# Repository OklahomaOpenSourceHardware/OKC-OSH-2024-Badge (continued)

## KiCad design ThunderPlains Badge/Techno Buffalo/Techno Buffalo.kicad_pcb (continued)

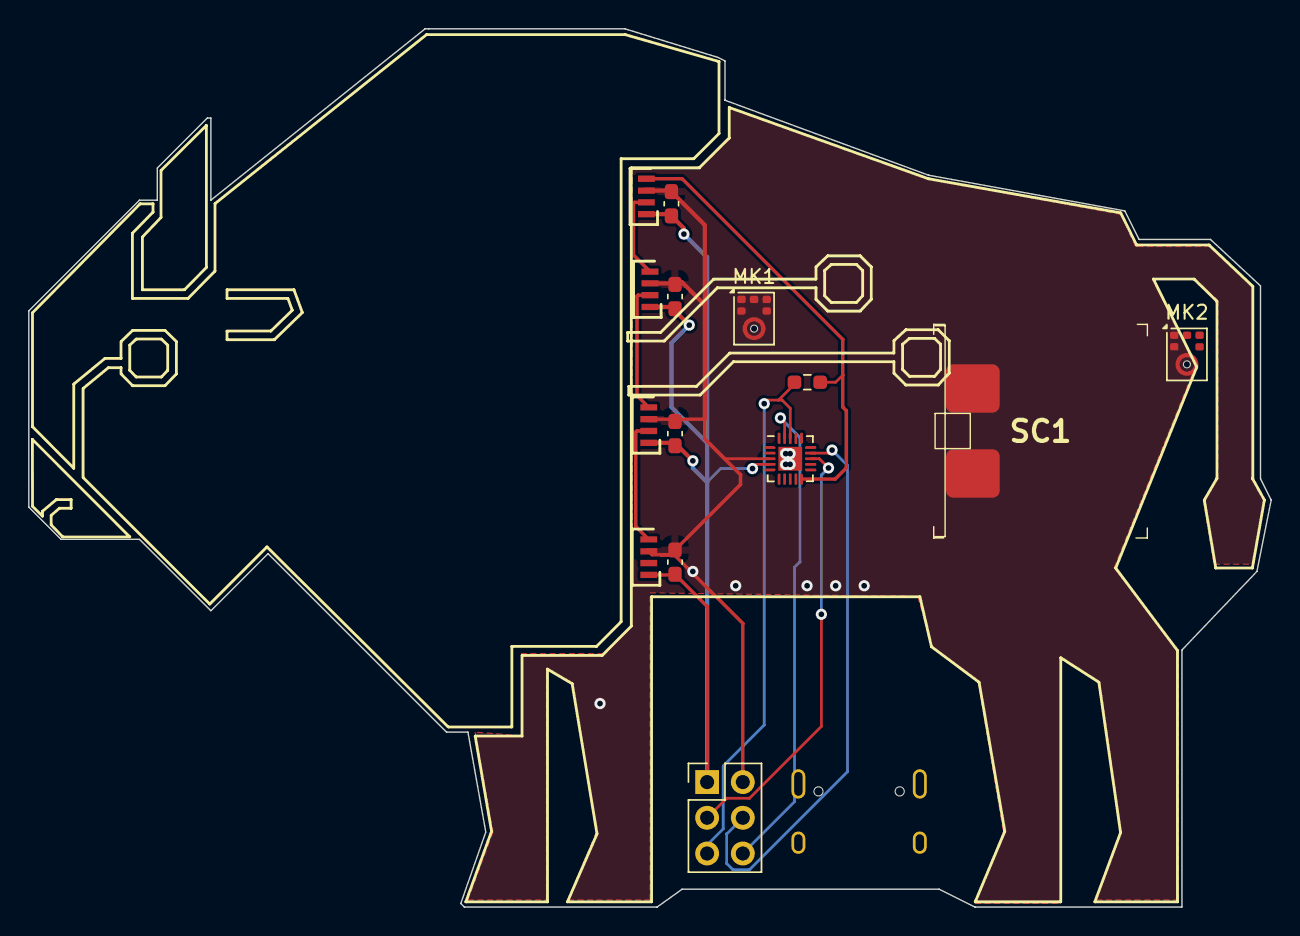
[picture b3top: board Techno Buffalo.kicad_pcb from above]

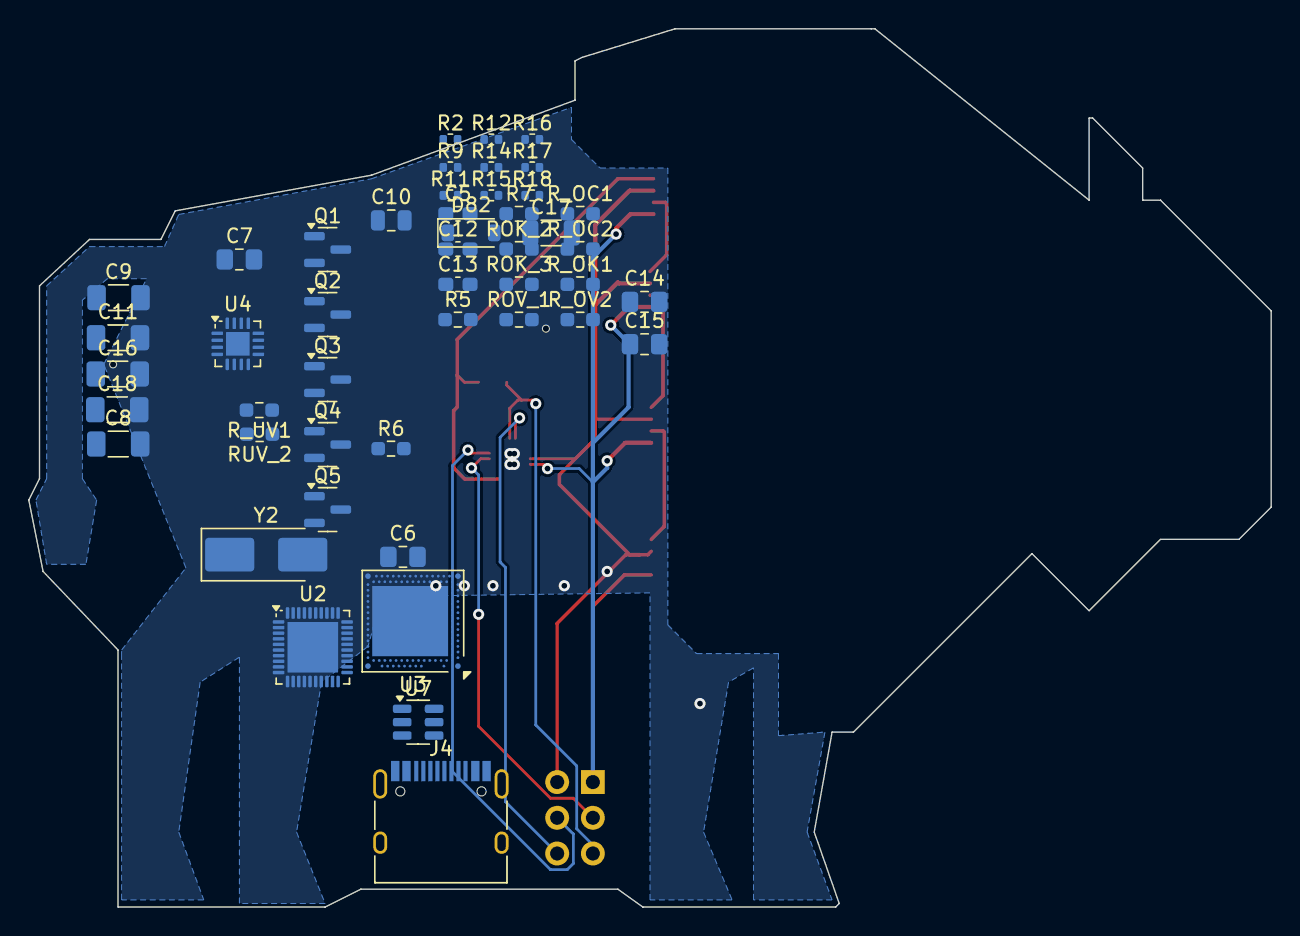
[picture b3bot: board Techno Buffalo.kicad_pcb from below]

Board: 2 copper layers, 88.4 x 62.5 mm, 61 parts (47 on the bottom side), 39 nets.

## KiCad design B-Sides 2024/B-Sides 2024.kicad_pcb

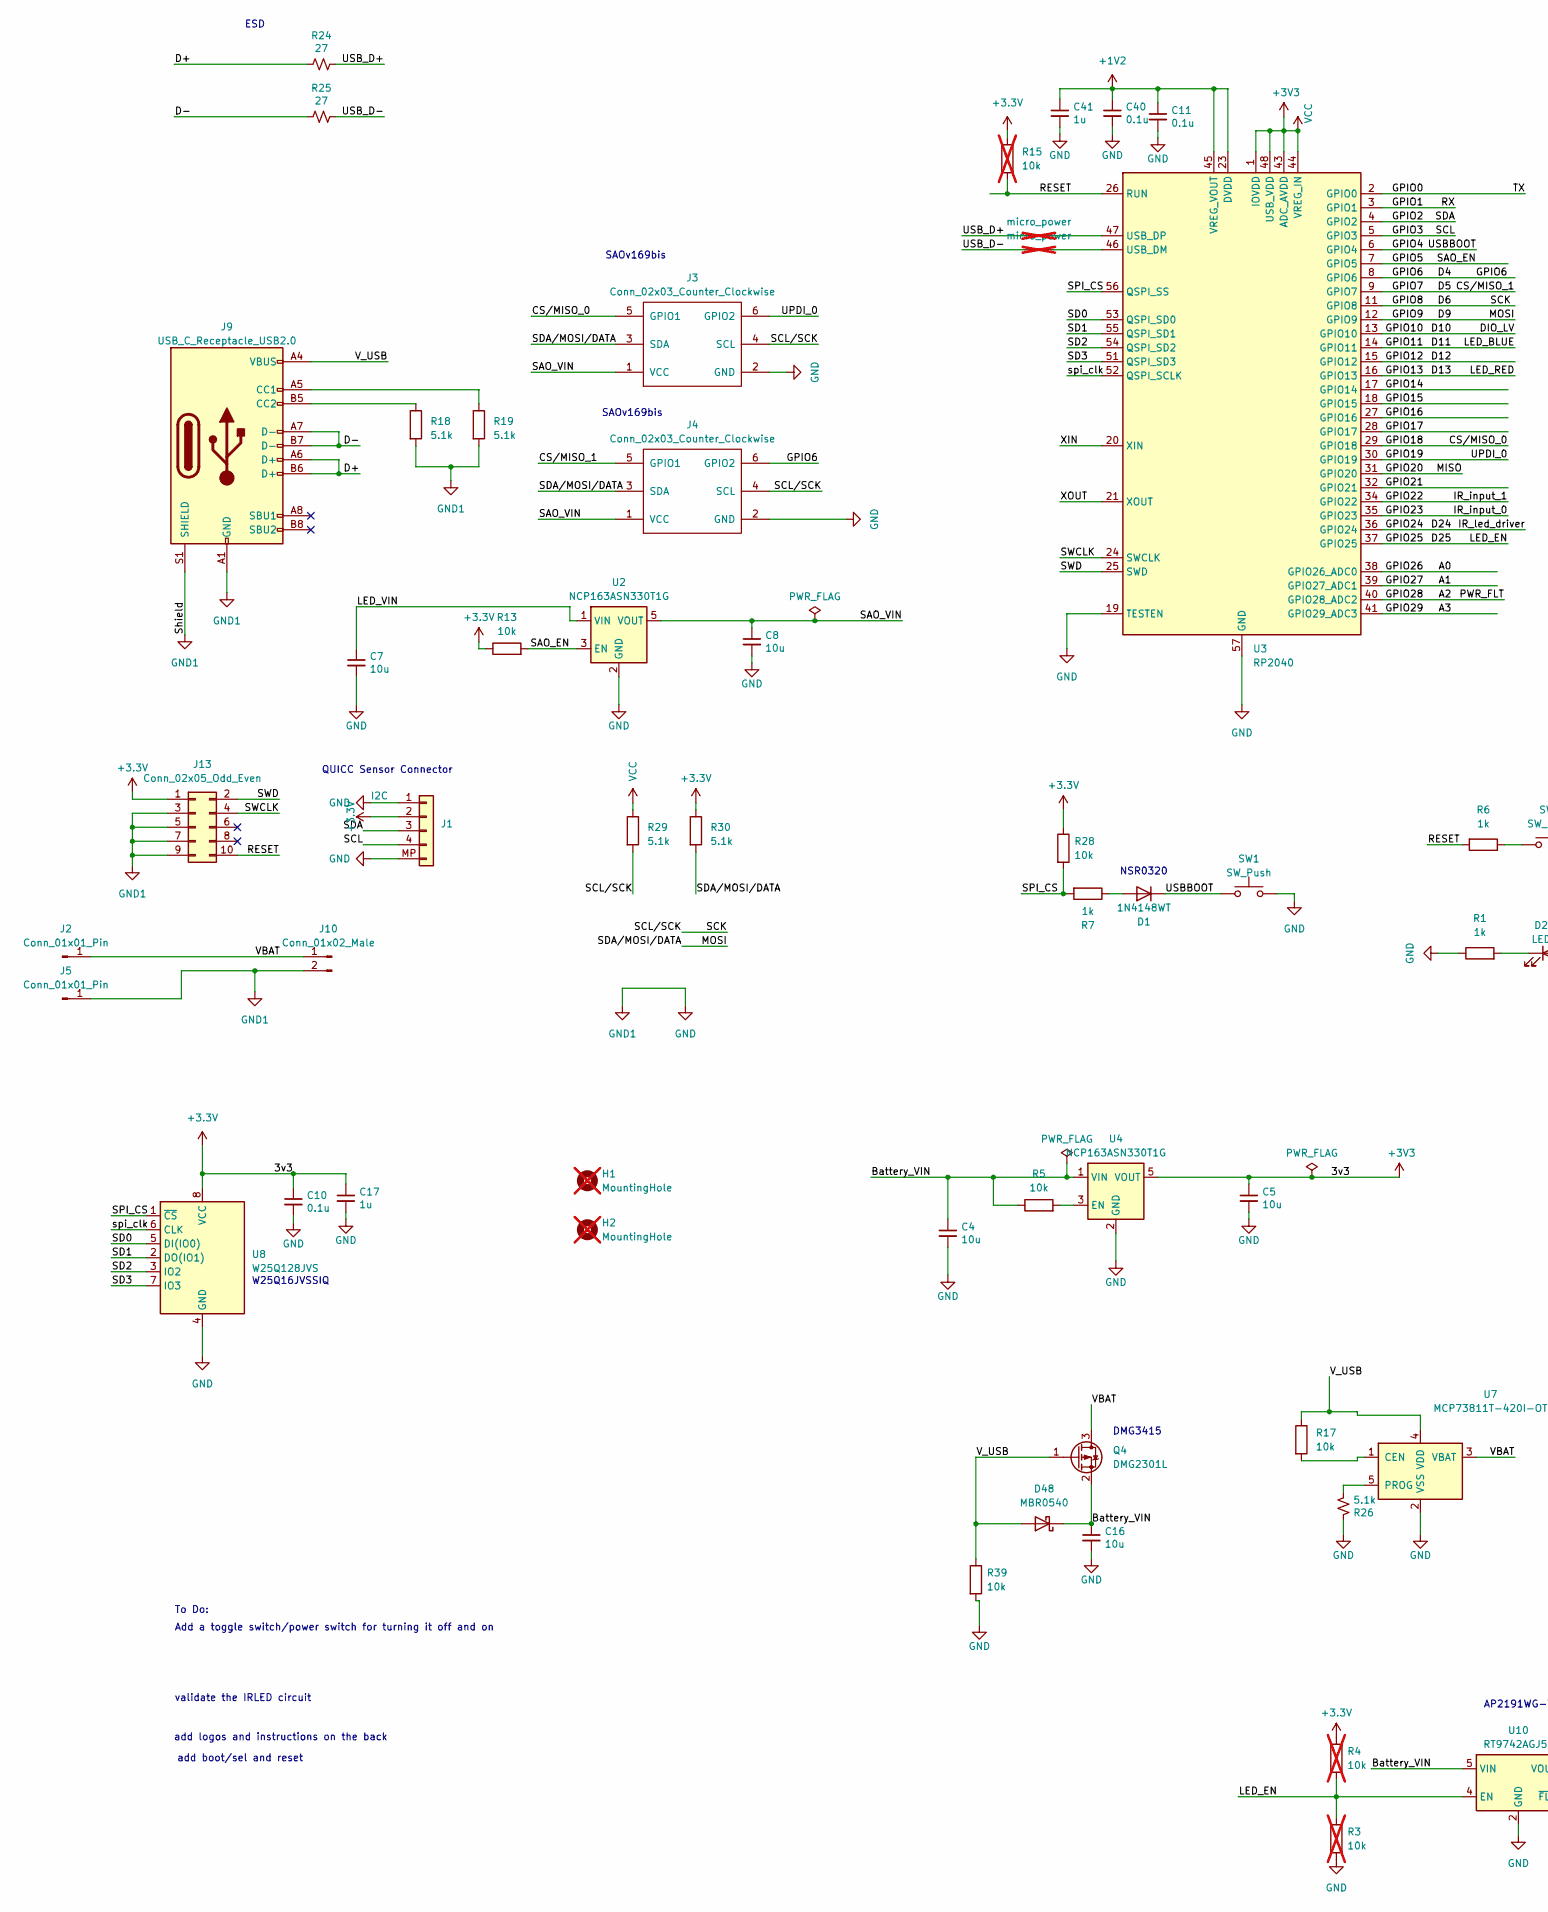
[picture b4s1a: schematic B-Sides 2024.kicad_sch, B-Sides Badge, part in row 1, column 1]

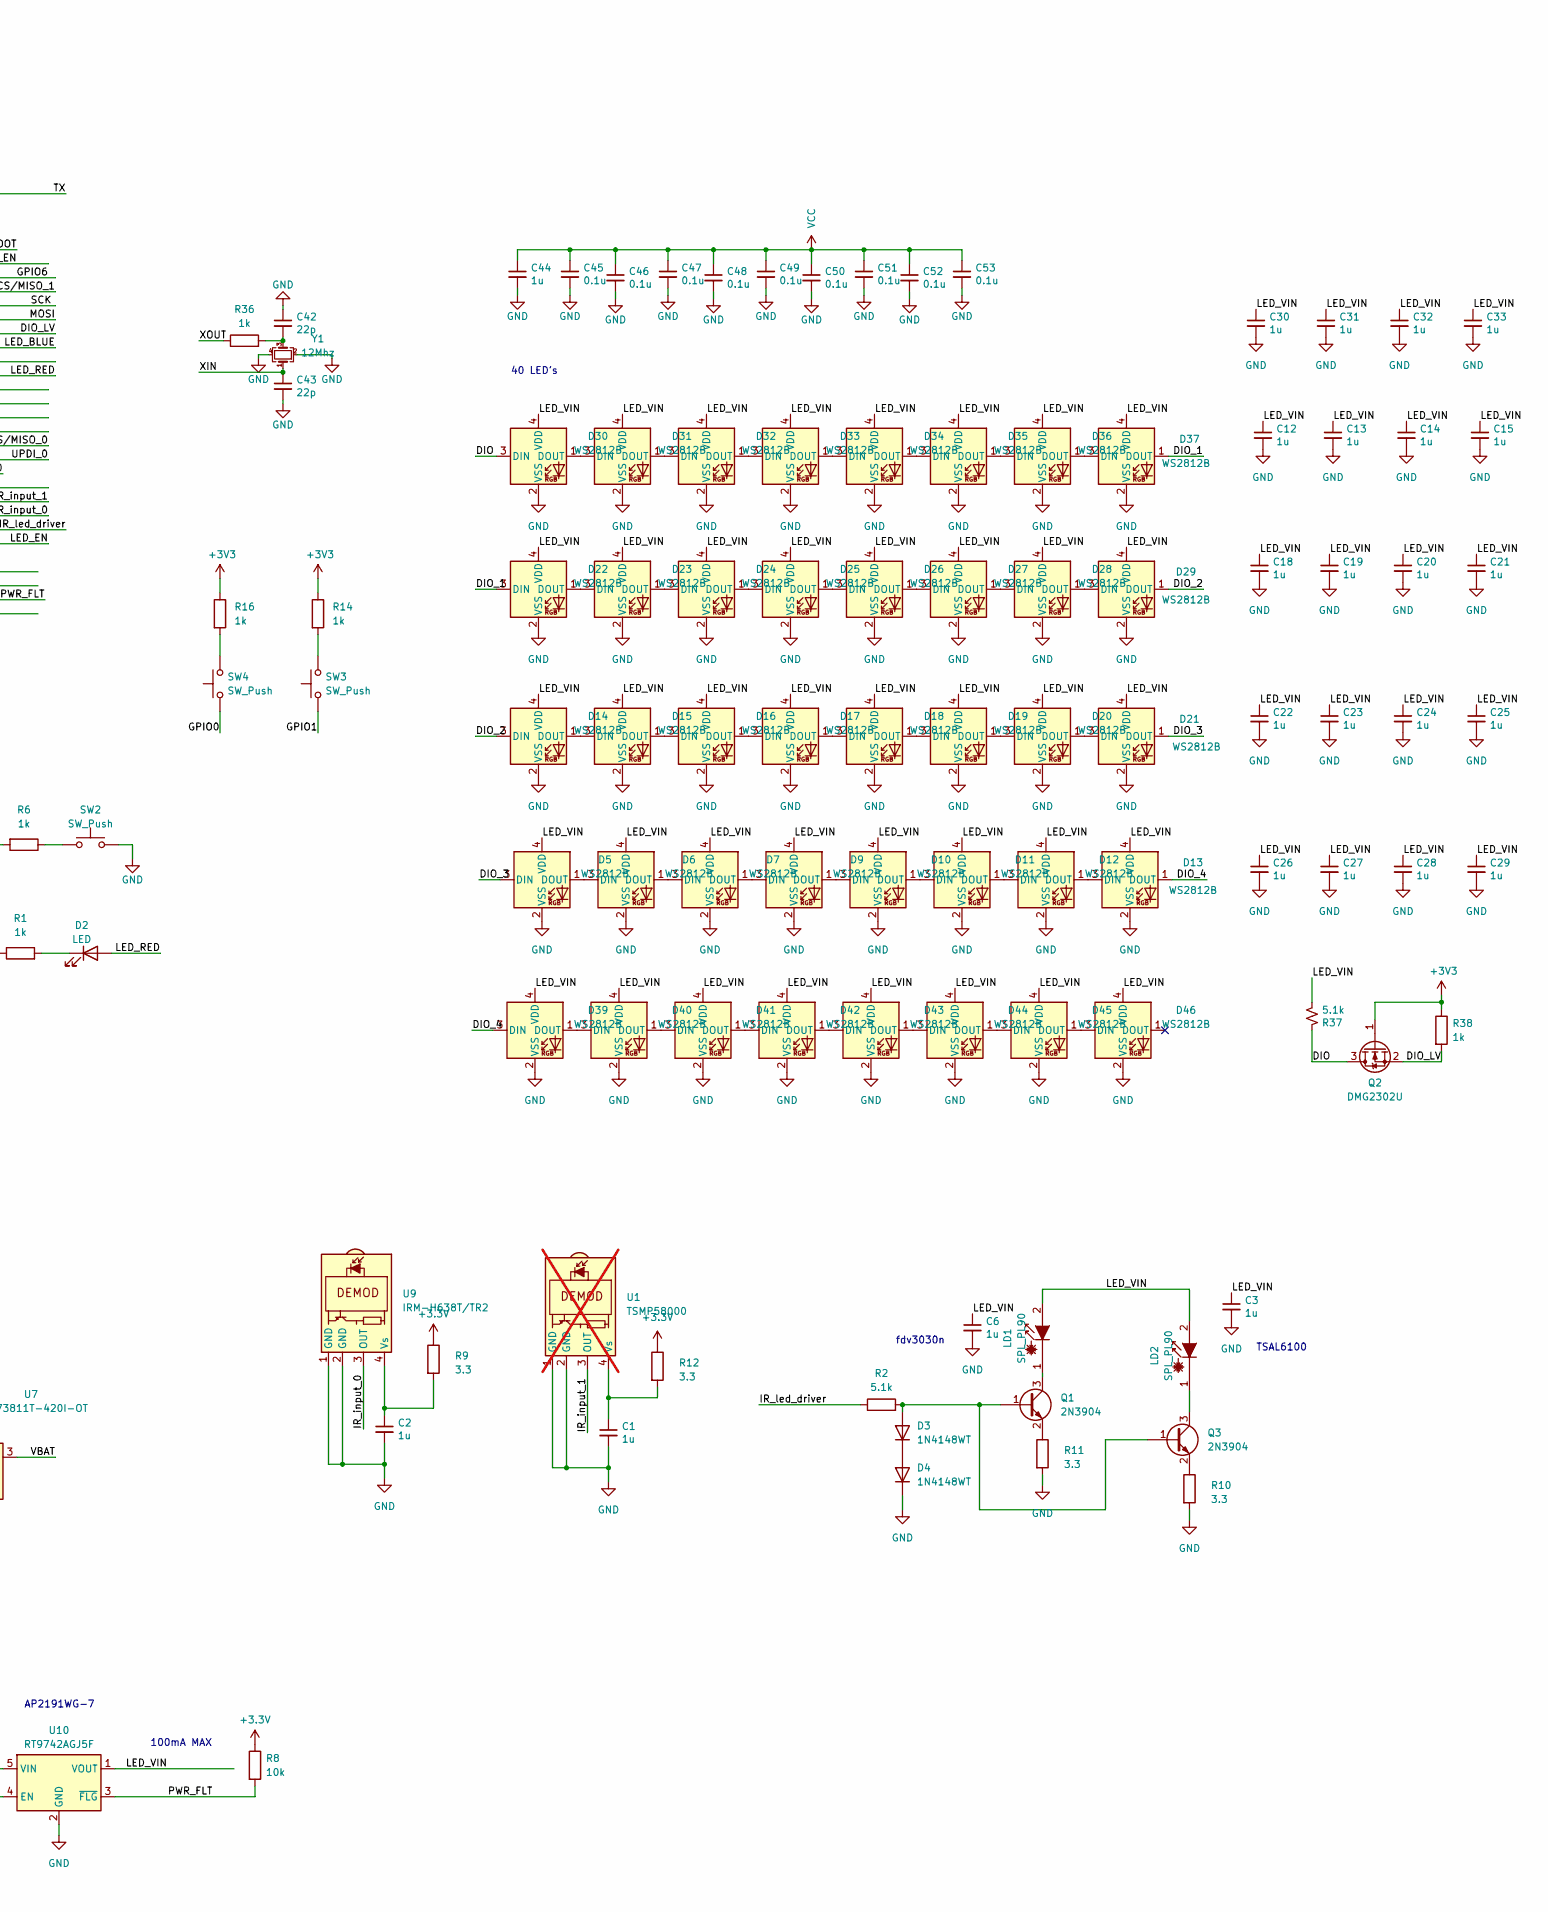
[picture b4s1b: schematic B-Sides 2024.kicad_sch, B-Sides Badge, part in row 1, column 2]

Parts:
C1, C2, C3, C6, C12, C13, C14, C15, C17, C18, C19, C20, C21, C22, C23, C24, C25, C26, C27, C28, C29, C30, C31, C32, C33, C41, C44: 1u; C_0402_1005Metric; PARTREV V3; Digikey Part Number 1276-1001-1-ND
C4, C5, C7, C8, C16: 10u; C_0805_2012Metric; LCSC C1713
C10, C11, C40, C45, C46, C47, C48, C49, C50, C51, C52, C53: 0.1u; C_0402_1005Metric; PARTREV V3; Digikey Part Number 1276-1001-1-ND
C42, C43: 22p; C_0402_1005Metric; PARTREV V3; Digikey Part Number 1276-1001-1-ND
D1, D3, D4: 1N4148WT; D_SOD-523; LCSC C727112
D2: LED; LED_0603_1608Metric_Pad1.05x0.95mm_HandSolder; LCSC C965799
D5, D6, D7, D9, D10, D11, D12, D13, D14, D15, D16, D17, D18, D19, D20, D21, D22, D23, D24, D25, D26, D27, D28, D29, D30, D31, D32, D33, D34, D35, D36, D37, D39, D40, D41, D42, D43, D44, D45, D46: WS2812B; LED_WS2812B-2020_PLCC4_2.0x2.0mm; Manufacturer_Part_Number WS2812B-2020; LCSC C965555
D48: MBR0540; D_SOD-123; LCSC C116159
H1, H2: MountingHole; MountingHole_4.3mm_M4_11mm_slot; not fitted
J1: I2C; JST_SH_SM04B-SRSS-TB_1x04-1MP_P1.00mm_Horizontal; LCSC C160404
J2, J5: Conn_01x01_Pin; Keystone 18650 clips_single; LCSC C2979182
J3, J4: Conn_02x03_Counter_Clockwise; Simple_Addon_v2-BADGE-2x3; LCSC C92272
J9: USB_C_Receptacle_USB2.0; USB_C_Receptacle_GCT_USB4105-xx-A_16P_TopMnt_Horizontal; LCSC C5117884
J10: Conn_01x02_Male; JST_PH_S2B-PH-K_1x02_P2.00mm_Horizontal; LCSC C173752
J13: Conn_02x05_Odd_Even; PinSocket_2x05_P1.27mm_Vertical_SMD; LCSC C2935458
LD1: SPL_PL90; LED_1206_3216Metric; LCSC C131280
LD2: SPL_PL90; LED_1206_3216Metric; LCSC C282224
NT5, NT6: micro_power; NetTie-2_SMD_Pad0.5mm; not fitted
Q1, Q3: 2N3904; SOT-23; LCSC C126908
Q2: DMG2302U; SOT-23; LCSC C460977
Q4: DMG2301L; SOT-23; LCSC C460976
R1, R6, R7, R14, R16, R36, R38: 1k; R_0402_1005Metric; LCSC C106235
R2, R18, R19, R29, R30: 5.1k; R_0402_1005Metric; LCSC C105872
R3, R4, R15: 10k; R_0402_1005Metric; LCSC C60490; not fitted
R5, R8, R13, R17, R28, R39: 10k; R_0402_1005Metric; LCSC C60490
R9, R10, R11, R12: 3.3; R_0402_1005Metric; LCSC C412900
R24, R25: 27; R_0402_1005Metric; Manufacturer_Part_Number RK73B1JTTDD270J; Mouser Part Number 660-RK73B1JTTDD270J
R26, R37: 5.1k; R_0402_1005Metric; Manufacturer_Part_Number CR0603-FX-5101ELF; Mouser Part Number 652-CR0603FX-5101ELF
SW1, SW2, SW3, SW4: SW_Push; SW_SPST_B3U-1000P; Manufacturer_Part_Number B3U-1000P; Digikey Part Number SW1020CT-ND
U1: TSMP58000; IRM-H638TTR2; Manufacturer_Part_Number IRM-H638T/TR2; LCSC C91447; not fitted
U2, U4: NCP163ASN330T1G; SOT-23-5; LCSC C156285
U3: RP2040; QFN-56-1EP_7x7mm_P0.4mm_EP3.2x3.2mm; LCSC C2040
U7: MCP73811T-420I-OT; SOT-23-5; LCSC C5280697
U8: W25Q128JVS; SOIC-8_5.23x5.23mm_P1.27mm; LCSC C82317
U9: IRM-H638T/TR2; IRM-H638TTR2; Manufacturer_Part_Number IRM-H638T/TR2; LCSC C91447
U10: RT9742AGJ5F; TSOT-23-5; LCSC C3001659
Y1: 12Mhz; Crystal_SMD_2520-4Pin_2.5x2.0mm; Manufacturer_Part_Number ECS-120-12-30B-AGM-TR; Mouser Part Number 520-120-12-30B-AGMT

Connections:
+1V2: C11.1, C40.1, C41.1, U3.23 (DVDD), U3.45 (VREG_VOUT), U3.50 (DVDD)
+3.3V: C5.1, C10.1, C17.1, C44.1, C45.1, C46.1, C47.1, C48.1, C49.1, C50.1, C51.1, C52.1, C53.1, J1.2, J13.1, Q2.1 (G), R4.1, R8.1, R9.1, R12.1, R13.1, R14.1, R15.2, R16.1, R28.1, R29.1, R30.1, R38.1, U3.1 (IOVDD), U3.10 (IOVDD), U3.22 (IOVDD), U3.33 (IOVDD), U3.42 (IOVDD), U3.43 (ADC_AVDD), U3.44 (VREG_IN), U3.48 (USB_VDD), U3.49 (IOVDD), U4.5 (VOUT), U8.8 (VCC)
/A0: U3.38 (GPIO26_ADC0)
/A1: U3.39 (GPIO27_ADC1)
/A2: R8.2, U3.40 (GPIO28_ADC2), U10.3 (~FLG)
/A3: U3.41 (GPIO29_ADC3)
/Battery_VIN: C4.1, C16.1, D48.1 (K), Q4.2 (S), R5.1, U4.1 (VIN), U10.5 (VIN)
/CS/MISO_0: J3.5 (GPIO1), U3.29 (GPIO18)
/CS/MISO_1: J4.5 (GPIO1), U3.9 (GPIO7)
/D4: J4.6 (GPIO2), U3.8 (GPIO6)
/D6: J3.4 (SCL), J4.4 (SCL), R29.2, U3.11 (GPIO8)
/D9: J3.3 (SDA), J4.3 (SDA), R30.2, U3.12 (GPIO9)
/D10: Q2.2 (S), R38.2, U3.13 (GPIO10)
/D11: U3.14 (GPIO11)
/D12: U3.15 (GPIO12)
/D13: D2.2 (A), U3.16 (GPIO13)
/D24: R2.1, U3.36 (GPIO24)
/D25: R3.1, R4.2, U3.37 (GPIO25), U10.4 (EN)
/D+: J9.A6 (D+), J9.B6 (D+), R24.1
/D-: J9.A7 (D-), J9.B7 (D-), R25.1
/DIO: D30.3 (DIN), Q2.3 (D), R37.1
/DIO_1: D22.3 (DIN), D37.1 (DOUT)
/DIO_2: D14.3 (DIN), D29.1 (DOUT)
/DIO_3: D5.3 (DIN), D21.1 (DOUT)
/DIO_4: D13.1 (DOUT), D39.3 (DIN)
/GPIO0: SW4.1, U3.2 (GPIO0)
/GPIO1: SW3.1, U3.3 (GPIO1)
/GPIO2: J1.3, U3.4 (GPIO2)
/GPIO3: J1.4, U3.5 (GPIO3)
/GPIO4: D1.1 (K), SW1.2, U3.6 (GPIO4)
/GPIO5: R13.2, U2.3 (EN), U3.7 (GPIO5)
/GPIO14: U3.17 (GPIO14)
/GPIO15: U3.18 (GPIO15)
/GPIO16: U3.27 (GPIO16)
/GPIO17: U3.28 (GPIO17)
/GPIO19: J3.6 (GPIO2), U3.30 (GPIO19)
/GPIO20: U3.31 (GPIO20)
/GPIO21: U3.32 (GPIO21)
/GPIO22: U1.3 (OUT), U3.34 (GPIO22)
/GPIO23: U3.35 (GPIO23), U9.3 (OUT)
/LED_VIN: C3.1, C6.1, C7.1, C12.1, C13.1, C14.1, C15.1, C18.1, C19.1, C20.1, C21.1, C22.1, C23.1, C24.1, C25.1, C26.1, C27.1, C28.1, C29.1, C30.1, C31.1, C32.1, C33.1, D5.4 (VDD), D6.4 (VDD), D7.4 (VDD), D9.4 (VDD), D10.4 (VDD), D11.4 (VDD), D12.4 (VDD), D13.4 (VDD), D14.4 (VDD), D15.4 (VDD), D16.4 (VDD), D17.4 (VDD), D18.4 (VDD), D19.4 (VDD), D20.4 (VDD), D21.4 (VDD), D22.4 (VDD), D23.4 (VDD), D24.4 (VDD), D25.4 (VDD), D26.4 (VDD), D27.4 (VDD), D28.4 (VDD), D29.4 (VDD), D30.4 (VDD), D31.4 (VDD), D32.4 (VDD), D33.4 (VDD), D34.4 (VDD), D35.4 (VDD), D36.4 (VDD), D37.4 (VDD), D39.4 (VDD), D40.4 (VDD), D41.4 (VDD), D42.4 (VDD), D43.4 (VDD), D44.4 (VDD), D45.4 (VDD), D46.4 (VDD), LD1.2 (A), LD2.2 (A), R37.2, U2.1 (VIN), U10.1 (VOUT)
/RESET: J13.10, R6.2, R15.1, U3.26 (RUN)
/SAO_VIN: C8.1, J3.1 (VCC), J4.1 (VCC), U2.5 (VOUT)
/SD0: U3.53 (QSPI_SD0), U8.5 (DI(IO0))
/SD1: U3.55 (QSPI_SD1), U8.2 (DO(IO1))
/SD2: U3.54 (QSPI_SD2), U8.3 (IO2)
/SD3: U3.51 (QSPI_SD3), U8.7 (IO3)
/SPI_CS: R7.2, R28.2, U3.56 (QSPI_SS), U8.1 (~CS)
/SWCLK: J13.4, U3.24 (SWCLK)
/SWD: J13.2, U3.25 (SWD)
/USB_D+: NT5.2, R24.2
/USB_D-: NT6.2, R25.2
/VBAT: J2.1, J10.1, Q4.3 (D), U7.3 (VBAT)
/V_USB: D48.2 (A), J9.A4 (VBUS), J9.A9 (VBUS), J9.B4 (VBUS), J9.B9 (VBUS), Q4.1 (G), R17.1, R39.1, U7.4 (VDD)
/XIN: C43.1, U3.20 (XIN), Y1.1
/XOUT: R36.1, U3.21 (XOUT)
/spi_clk: U3.52 (QSPI_SCLK), U8.6 (CLK)
GND: C1.2, C2.2, C3.2, C4.2, C5.2, C6.2, C7.2, C8.2, C10.2, C11.2, C12.2, C13.2, C14.2, C15.2, C16.2, C17.2, C18.2, C19.2, C20.2, C21.2, C22.2, C23.2, C24.2, C25.2, C26.2, C27.2, C28.2, C29.2, C30.2, C31.2, C32.2, C33.2, C40.2, C41.2, C42.1, C43.2, C44.2, C45.2, C46.2, C47.2, C48.2, C49.2, C50.2, C51.2, C52.2, C53.2, D4.1 (K), D5.2 (VSS), D6.2 (VSS), D7.2 (VSS), D9.2 (VSS), D10.2 (VSS), D11.2 (VSS), D12.2 (VSS), D13.2 (VSS), D14.2 (VSS), D15.2 (VSS), D16.2 (VSS), D17.2 (VSS), D18.2 (VSS), D19.2 (VSS), D20.2 (VSS), D21.2 (VSS), D22.2 (VSS), D23.2 (VSS), D24.2 (VSS), D25.2 (VSS), D26.2 (VSS), D27.2 (VSS), D28.2 (VSS), D29.2 (VSS), D30.2 (VSS), D31.2 (VSS), D32.2 (VSS), D33.2 (VSS), D34.2 (VSS), D35.2 (VSS), D36.2 (VSS), D37.2 (VSS), D39.2 (VSS), D40.2 (VSS), D41.2 (VSS), D42.2 (VSS), D43.2 (VSS), D44.2 (VSS), D45.2 (VSS), D46.2 (VSS), J1.1, J1.MP (Pin_5), J3.2 (GND), J4.2 (GND), J5.1, J9.A1 (GND), J9.A12 (GND), J9.B1 (GND), J9.B12 (GND), J9.S1 (SHIELD), J10.2, J13.3, J13.5, J13.7, J13.9, R1.1, R3.2, R10.2, R11.2, R18.2, R19.2, R26.1, R39.2, SW1.1, SW2.2, U1.1 (GND), U1.2 (GND), U2.2 (GND), U3.19 (TESTEN), U3.57 (GND), U4.2 (GND), U7.2 (VSS), U8.4 (GND), U9.1 (GND), U9.2 (GND), U10.2 (GND), Y1.2, Y1.4
unnamed: C42.2, R36.2, Y1.3
unnamed: D1.2 (A), R7.1
unnamed: D2.1 (K), R1.2
unnamed: D3.2 (A), Q1.1 (B), Q3.1 (B), R2.2
unnamed: D3.1 (K), D4.2 (A)
unnamed: D5.1 (DOUT), D6.3 (DIN)
unnamed: D6.1 (DOUT), D7.3 (DIN)
unnamed: D7.1 (DOUT), D9.3 (DIN)
unnamed: D9.1 (DOUT), D10.3 (DIN)
unnamed: D10.1 (DOUT), D11.3 (DIN)
unnamed: D11.1 (DOUT), D12.3 (DIN)
unnamed: D12.1 (DOUT), D13.3 (DIN)
unnamed: D14.1 (DOUT), D15.3 (DIN)
unnamed: D15.1 (DOUT), D16.3 (DIN)
unnamed: D16.1 (DOUT), D17.3 (DIN)
unnamed: D17.1 (DOUT), D18.3 (DIN)
unnamed: D18.1 (DOUT), D19.3 (DIN)
unnamed: D19.1 (DOUT), D20.3 (DIN)
unnamed: D20.1 (DOUT), D21.3 (DIN)
unnamed: D22.1 (DOUT), D23.3 (DIN)
unnamed: D23.1 (DOUT), D24.3 (DIN)
unnamed: D24.1 (DOUT), D25.3 (DIN)
unnamed: D25.1 (DOUT), D26.3 (DIN)
unnamed: D26.1 (DOUT), D27.3 (DIN)
unnamed: D27.1 (DOUT), D28.3 (DIN)
unnamed: D28.1 (DOUT), D29.3 (DIN)
unnamed: D30.1 (DOUT), D31.3 (DIN)
unnamed: D31.1 (DOUT), D32.3 (DIN)
unnamed: D32.1 (DOUT), D33.3 (DIN)
unnamed: D33.1 (DOUT), D34.3 (DIN)
unnamed: D34.1 (DOUT), D35.3 (DIN)
unnamed: D35.1 (DOUT), D36.3 (DIN)
unnamed: D36.1 (DOUT), D37.3 (DIN)
unnamed: D39.1 (DOUT), D40.3 (DIN)
unnamed: D40.1 (DOUT), D41.3 (DIN)
unnamed: D41.1 (DOUT), D42.3 (DIN)
unnamed: D42.1 (DOUT), D43.3 (DIN)
unnamed: D43.1 (DOUT), D44.3 (DIN)
unnamed: D44.1 (DOUT), D45.3 (DIN)
unnamed: D45.1 (DOUT), D46.3 (DIN)
unnamed: J9.A5 (CC1), R19.1
unnamed: J9.B5 (CC2), R18.1
unnamed: LD1.1 (C), Q1.3 (C)
unnamed: LD2.1 (C), Q3.3 (C)
unnamed: Q1.2 (E), R11.1
unnamed: Q3.2 (E), R10.1
unnamed: R6.1, SW2.1
unnamed: R14.2, SW3.2
unnamed: R16.2, SW4.2
unnamed: C1.1, R12.2, U1.4 (Vs)
unnamed: NT6.1, U3.46 (USB_DM)
unnamed: NT5.1, U3.47 (USB_DP)
unnamed: R5.2, U4.3 (EN)
unnamed: R17.2, U7.1 (CEN)
unnamed: R26.2, U7.5 (PROG)
unnamed: C2.1, R9.2, U9.4 (Vs)

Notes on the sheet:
NSR0320
fdv3030n
SAOv169bis
validate the IRLED circuit
QUICC Sensor Connector
TSAL6100
DMG3415
ESD
To Do:
W25Q16JVSSIQ
Add a toggle switch/power switch for turning it off and on
100mA MAX
add boot/sel and reset
add logos and instructions on the back
40 LED's
AP2191WG-7

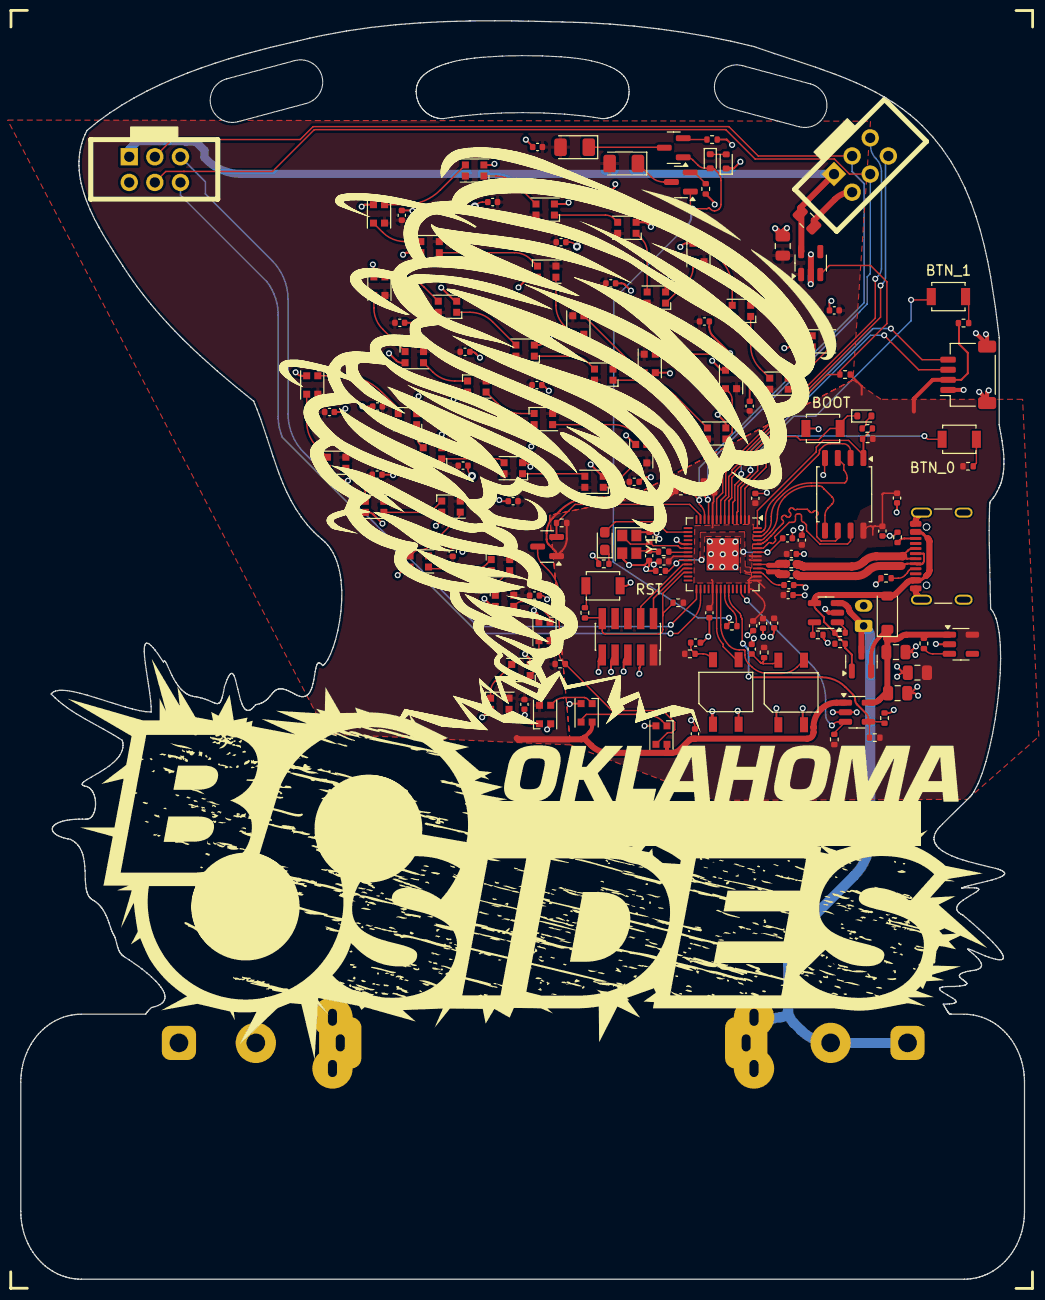
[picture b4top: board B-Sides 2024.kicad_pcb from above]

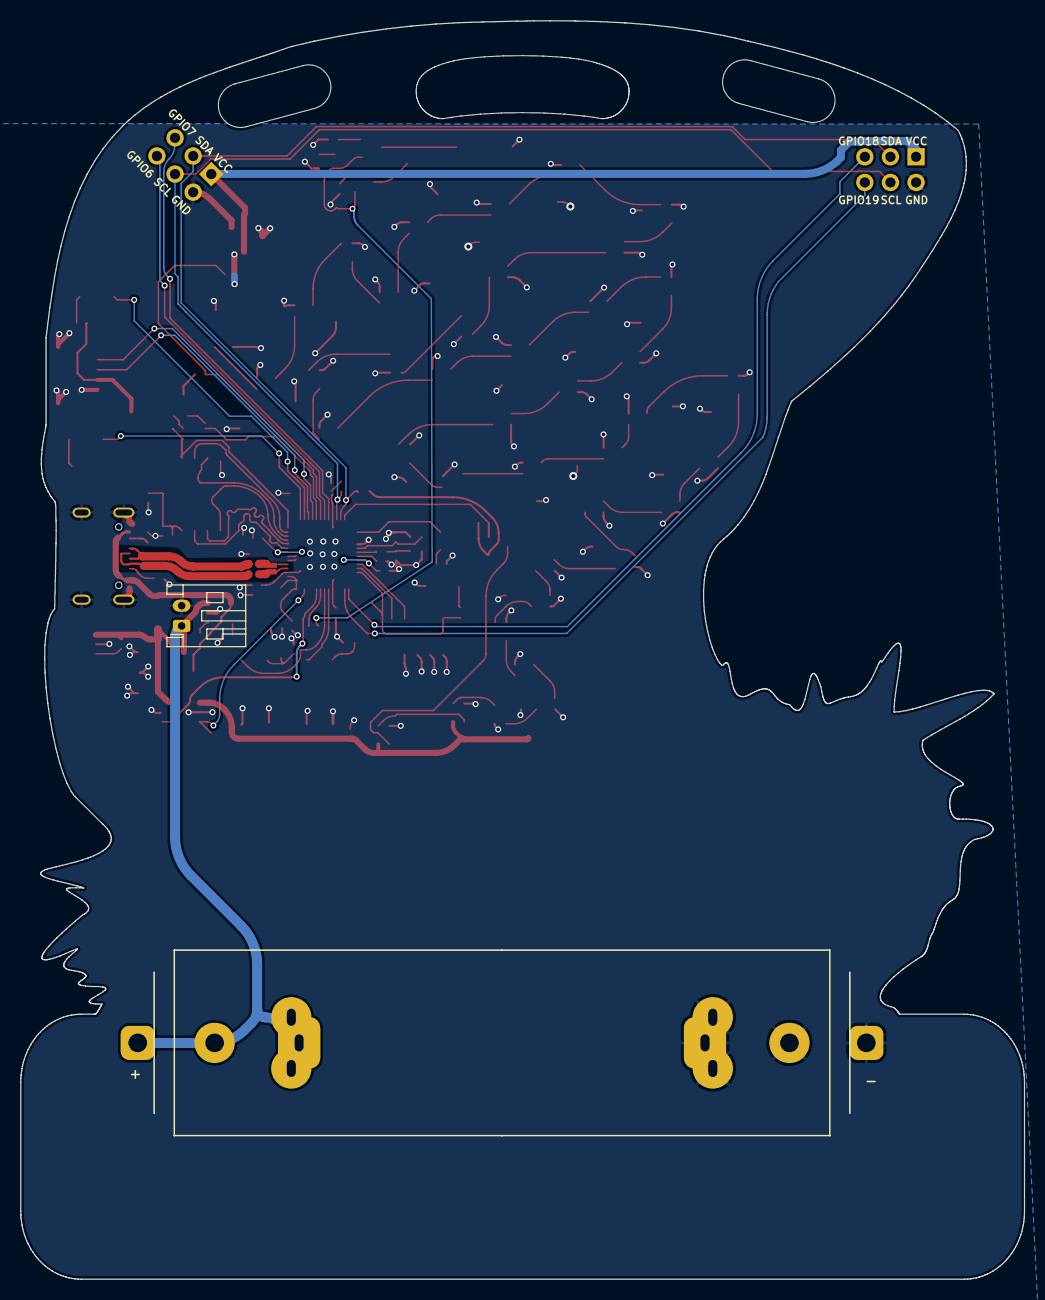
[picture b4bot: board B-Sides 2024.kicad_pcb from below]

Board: 2 copper layers, 99.5 x 124.8 mm, 151 parts (3 on the bottom side), 103 nets.

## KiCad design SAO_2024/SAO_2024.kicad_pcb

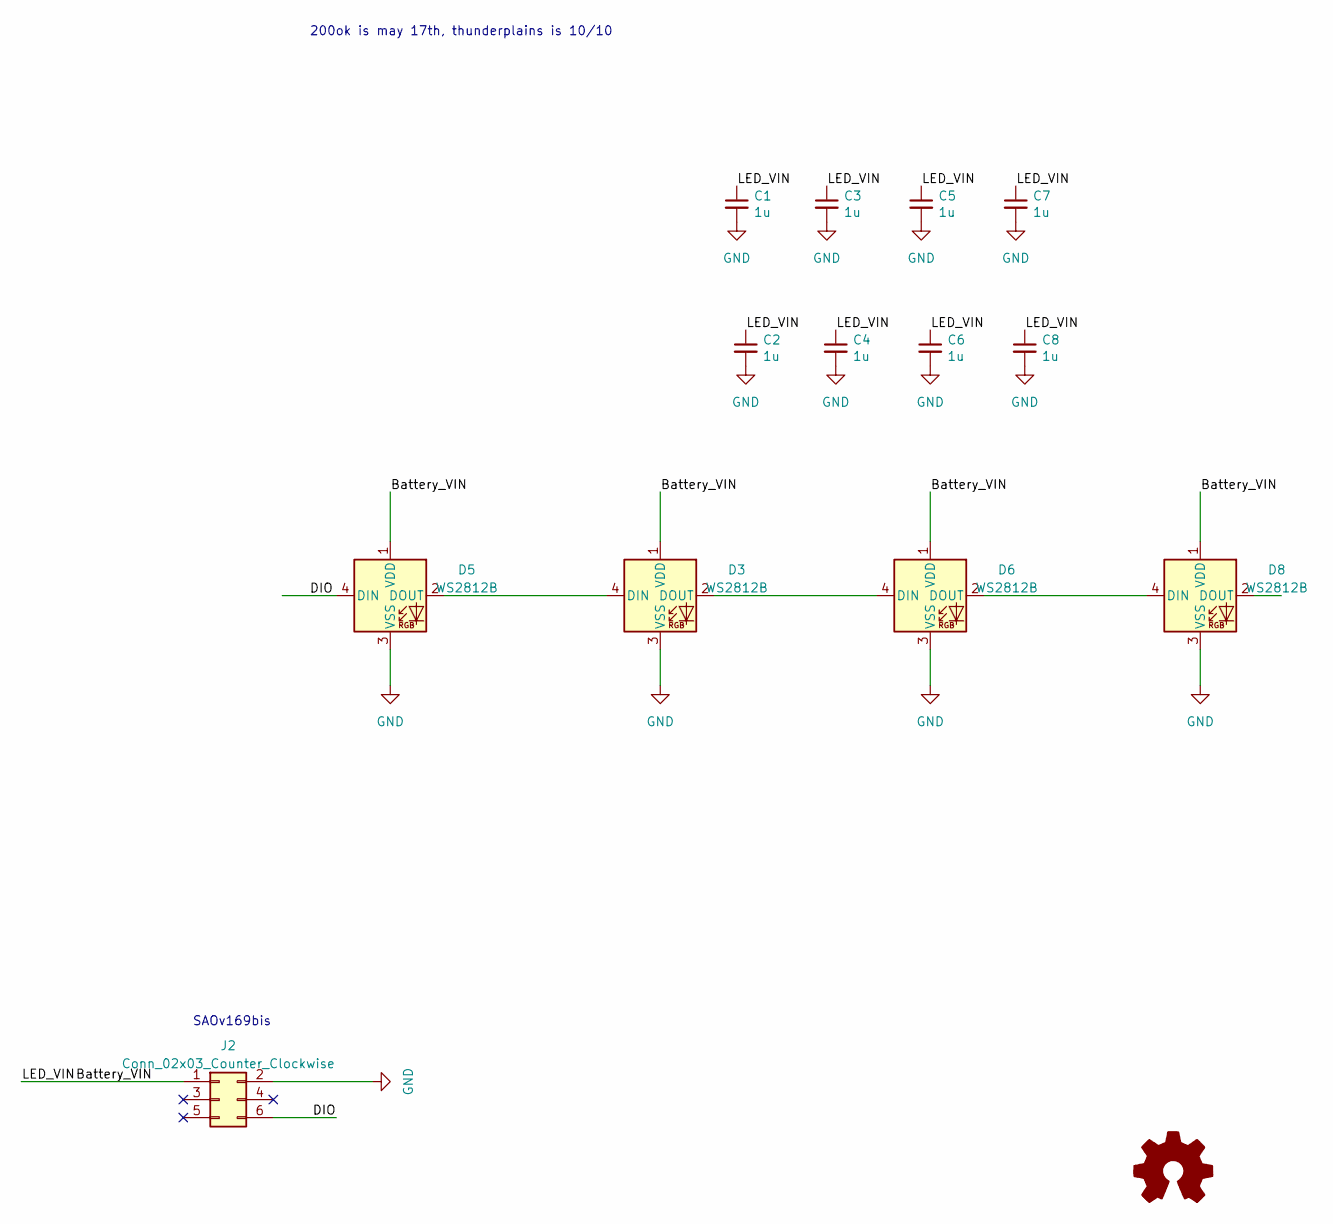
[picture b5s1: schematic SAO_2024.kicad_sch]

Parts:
C1, C2, C3, C4, C5, C6, C7, C8: 1u; C_0402_1005Metric; PARTREV V3; Digikey Part Number 1276-1001-1-ND
D3, D5, D6, D8: WS2812B; LED_WS2812B_PLCC4_5.0x5.0mm_P3.2mm; LCSC C114586
J2: Conn_02x03_Counter_Clockwise; PinHeader_2x03_P2.54mm_Vertical_SMD; LCSC C5160759

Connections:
/Battery_VIN: C1.1, C2.1, C3.1, C4.1, C5.1, C6.1, C7.1, C8.1, D3.1 (VDD), D5.1 (VDD), D6.1 (VDD), D8.1 (VDD), J2.1
/DIO: D5.4 (DIN), J2.6
GND: C1.2, C2.2, C3.2, C4.2, C5.2, C6.2, C7.2, C8.2, D3.3 (VSS), D5.3 (VSS), D6.3 (VSS), D8.3 (VSS), J2.2
unnamed: D3.4 (DIN), D5.2 (DOUT)
unnamed: D3.2 (DOUT), D6.4 (DIN)
unnamed: D6.2 (DOUT), D8.4 (DIN)

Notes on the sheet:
SAOv169bis
200ok is may 17th, thunderplains is 10/10

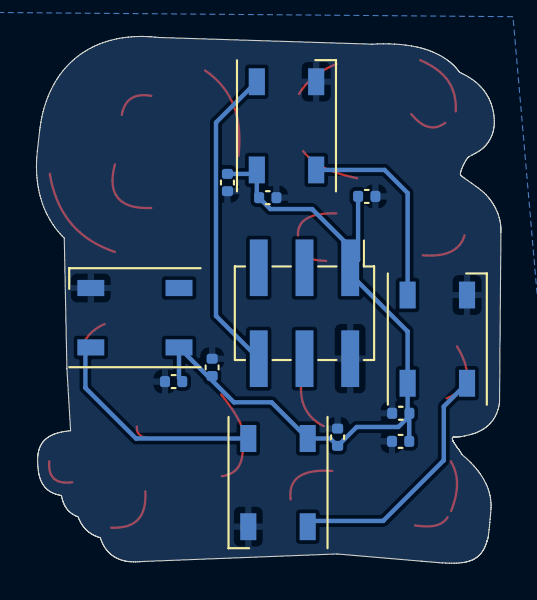
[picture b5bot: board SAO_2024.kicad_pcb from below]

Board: 2 copper layers, 25.8 x 29.3 mm, 13 parts (13 on the bottom side), 6 nets.

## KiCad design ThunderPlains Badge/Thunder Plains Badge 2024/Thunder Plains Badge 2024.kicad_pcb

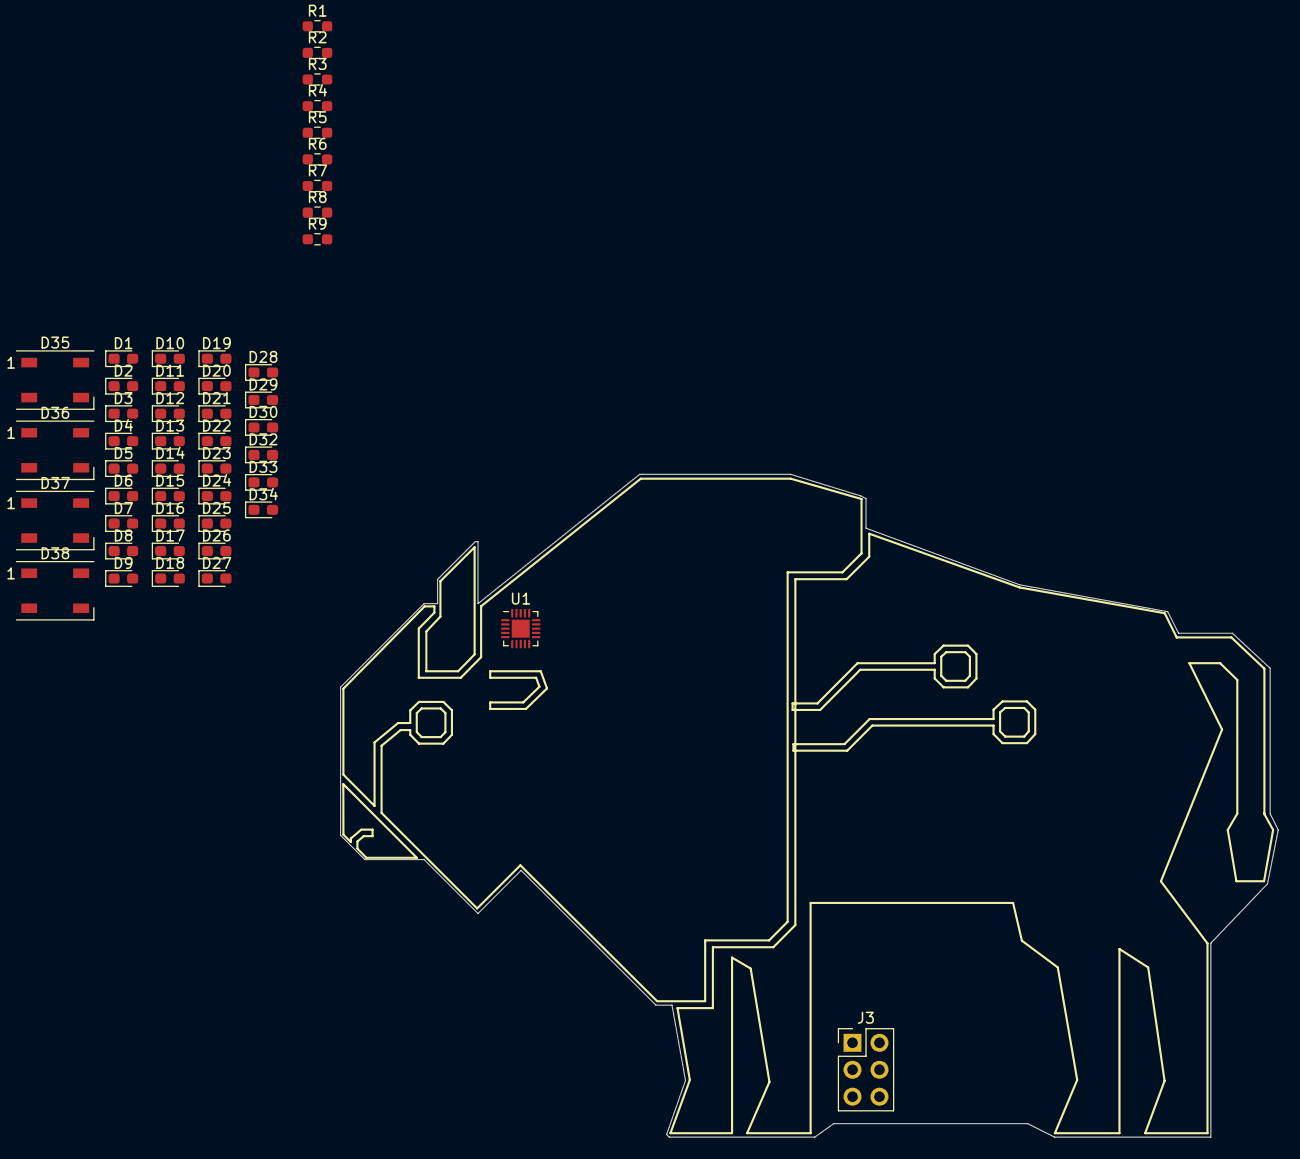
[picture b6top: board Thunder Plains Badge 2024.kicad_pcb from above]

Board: 2 copper layers, 88.4 x 62.5 mm, 48 parts (0 on the bottom side), 28 nets, no tracks yet.

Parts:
D1, D2, D3, D4, D5, D6, D7, D8, D9, D10, D11, D12, D13, D14, D15, D16, D17, D18, D19, D20, D21, D22, D23, D24, D25, D26, D27, D28, D29, D30, D32, D33, D34: LED; LED_0603_1608Metric_Pad1.05x0.95mm_HandSolder
D35, D36, D37, D38: WS2812B; LED_WS2812B_PLCC4_5.0x5.0mm_P3.2mm
J3: Conn_02x03_Counter_Clockwise; PinHeader_2x03_P2.54mm_Vertical
R1, R2, R3, R4, R5, R6, R7, R8, R9: 220; R_0603_1608Metric_Pad0.98x0.95mm_HandSolder
U1: ATtiny816-M; VQFN-20-1EP_3x3mm_P0.4mm_EP1.7x1.7mm

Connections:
/Battery_VIN: D35.1 (VDD), D36.1 (VDD), D37.1 (VDD), D38.1 (VDD), J3.1, U1.4 (VCC)
/CS/MISO: J3.5, U1.18 (PC3)
/Charlie_Plex_1: R1.2, U1.20 (PA1)
/Charlie_Plex_2: R2.2, U1.1 (PA2)
/Charlie_Plex_3: R3.2, U1.2 (PA3)
/Charlie_Plex_4: R4.2, U1.5 (PA4)
/Charlie_Plex_5: R5.2, U1.6 (PA5)
/Charlie_Plex_6: R6.2, U1.7 (PA6)
/DIO: D35.4 (DIN), U1.10 (PB4)
/LED_BLUE: D34.2 (A), U1.17 (PC2)
/LED_GREEN: D33.2 (A), U1.16 (PC1)
/LED_RED: D32.2 (A), U1.15 (PC0)
/SCL/SCK: J3.4, U1.14 (PB0)
/SDA/MOSI/DATA: J3.3, U1.13 (PB1)
/UPDI: J3.6, U1.19 (~RESET/PA0)
GND: D35.3 (VSS), D36.3 (VSS), D37.3 (VSS), D38.3 (VSS), J3.2, R7.2, R8.2, R9.2, U1.3 (GND), U1.21 (GND)
unnamed: D1.2 (A), D2.1 (K), D7.2 (A), D8.1 (K), D13.2 (A), D14.1 (K), D16.1 (K), D20.2 (A), D25.2 (A), D30.1 (K), R2.1
unnamed: D1.1 (K), D6.1 (K), D11.2 (A), D12.1 (K), D18.2 (A), D19.1 (K), D23.2 (A), D24.1 (K), D29.2 (A), D30.2 (A), R1.1
unnamed: D5.2 (A), D10.2 (A), D14.2 (A), D15.1 (K), D19.2 (A), D20.1 (K), D22.2 (A), D23.1 (K), D26.1 (K), D27.1 (K), R6.1
unnamed: D3.2 (A), D4.1 (K), D9.2 (A), D10.1 (K), D15.2 (A), D16.2 (A), D24.2 (A), D25.1 (K), D28.1 (K), D29.1 (K), R4.1
unnamed: D2.2 (A), D3.1 (K), D6.2 (A), D7.1 (K), D11.1 (K), D17.1 (K), D21.2 (A), D22.1 (K), D27.2 (A), D28.2 (A), R3.1
unnamed: D4.2 (A), D5.1 (K), D8.2 (A), D9.1 (K), D12.2 (A), D13.1 (K), D17.2 (A), D18.1 (K), D21.1 (K), D26.2 (A), R5.1
unnamed: D32.1 (K), R7.1
unnamed: D33.1 (K), R8.1
unnamed: D34.1 (K), R9.1
unnamed: D35.2 (DOUT), D36.4 (DIN)
unnamed: D36.2 (DOUT), D37.4 (DIN)
unnamed: D37.2 (DOUT), D38.4 (DIN)
